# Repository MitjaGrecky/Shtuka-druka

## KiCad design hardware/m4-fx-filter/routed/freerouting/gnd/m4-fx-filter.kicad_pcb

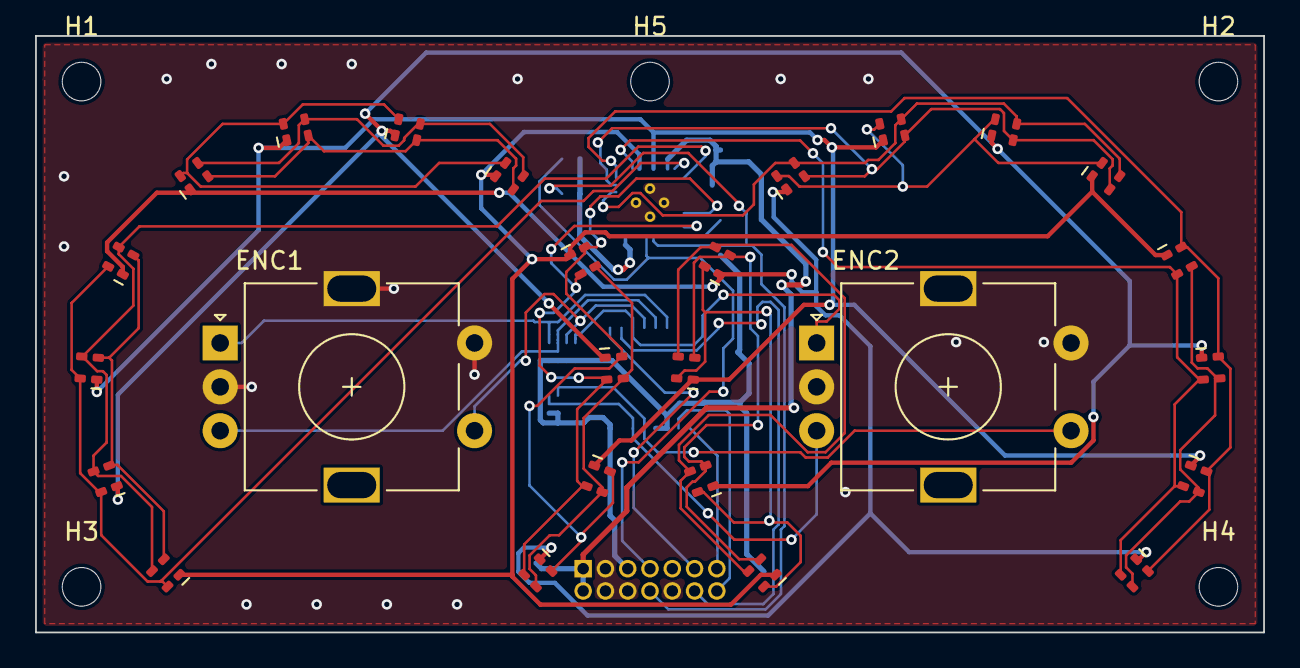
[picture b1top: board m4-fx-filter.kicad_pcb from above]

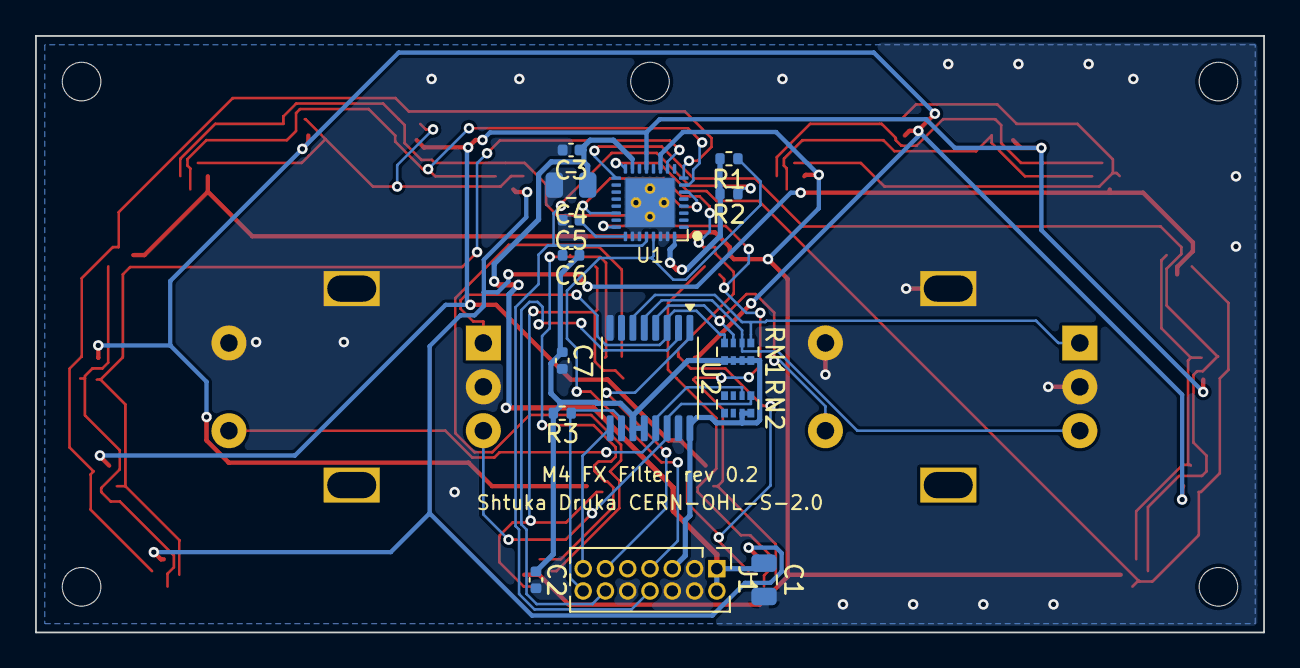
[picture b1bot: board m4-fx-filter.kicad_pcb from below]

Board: 2 copper layers, 70.0 x 34.0 mm, 46 parts (15 on the bottom side), 38 nets.

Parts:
C1: 10u; C_0805_2012Metric
C2, C3, C5: 1u; C_0402_1005Metric
C4: 4.7u; C_0805_2012Metric
C6: 1n; C_0402_1005Metric
C7: 100n; C_0402_1005Metric
D1, D2, D3, D4, D5, D6, D7, D8, D9, D10, D11, D12, D13, D14, D15, D16, D17, D18, D19, D20, D21, D22, D23, D24: XL-1615RGBC-RF; LED_RGB_XL-1615RGBC_1.6x1.5mm
ENC1, ENC2: EC11E smooth, switch; RotaryEncoder_Alps_EC11E-Switch_Vertical_H20mm_Ring
H1, H2, H3, H4, H5: M2; MountingHole_2.2mm_M2
J1: Module bus 2x7 1.27; PinHeader_2x07_P1.27mm_Vertical
R1, R2: 4.7k; R_0402_1005Metric
R3: 10k; R_0402_1005Metric
RN1, RN2: 4x10k; R_Array_Convex_4x0402
U1: LP5864RSMR; VQFN-32-1EP_4x4mm_P0.4mm_EP2.8x2.8mm
U2: 74HC165PW; TSSOP-16_4.4x5mm_P0.65mm

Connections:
+3V3: C2.1, C6.1, C7.1, J1.5, R1.2, R2.2, R3.2, RN1.5, RN1.6, RN1.7, RN1.8, RN2.7, RN2.8, U1.32, U2.11, U2.12, U2.16
+5V: C1.1, C3.1, C4.1, J1.1, J1.2, U1.1, U1.15
/A_CS0: D13.1, D14.1, D15.1, D16.1, U1.2
/A_CS1: D13.3, D14.3, D15.3, D16.3, U1.3
/A_CS2: D13.4, D14.4, D15.4, D16.4, U1.4
/A_CS3: D17.1, D18.1, D19.1, D20.1, U1.5
/A_CS4: D17.3, D18.3, D19.3, D20.3, U1.6
/A_CS5: D17.4, D18.4, D19.4, D20.4, U1.7
/A_CS6: D21.1, D22.1, D23.1, D24.1, U1.8
/A_CS7: D21.3, D22.3, D23.3, D24.3, U1.9
/A_CS8: D21.4, D22.4, D23.4, D24.4, U1.10
/A_CS9: D1.1, D2.1, D3.1, D4.1, U1.16
/A_CS10: D1.3, D2.3, D3.3, D4.3, U1.17
/A_CS11: D1.4, D2.4, D3.4, D4.4, U1.18
/A_CS12: D5.1, D6.1, D7.1, D8.1, U1.19
/A_CS13: D5.3, D6.3, D7.3, D8.3, U1.20
/A_CS14: D5.4, D6.4, D7.4, D8.4, U1.21
/A_CS15: D9.1, D10.1, D11.1, D12.1, U1.22
/A_CS16: D9.3, D10.3, D11.3, D12.3, U1.23
/A_CS17: D9.4, D10.4, D11.4, D12.4, U1.24
/A_SW0: D1.2, D8.2, D9.2, D13.2, D20.2, D21.2, U1.11
/A_SW1: D2.2, D7.2, D10.2, D14.2, D19.2, D22.2, U1.12
/A_SW2: D3.2, D6.2, D11.2, D15.2, D18.2, D23.2, U1.13
/A_SW3: D4.2, D5.2, D12.2, D16.2, D17.2, D24.2, U1.14
/A_VCAP: C5.1, U1.25
/E0_A: ENC1.A, RN1.1, U2.6
/E0_B: ENC1.B, RN1.2, U2.5
/E0_SW: ENC1.S1, RN1.3, U2.4
/E1_A: ENC2.A, RN1.4, U2.3
/E1_B: ENC2.B, RN2.1, U2.14
/E1_SW: ENC2.S1, RN2.2, U2.13
/SCL: J1.8, R2.1, U1.28
/SDA: J1.7, R1.1, U1.29
/SR_CLK: J1.12, U2.2
/SR_IN: J1.14, R3.1, U2.10
/SR_OUT: J1.13, U2.9
/~SR_LOAD: J1.11, U2.1
GND: C1.2, C2.2, C3.2, C4.2, C5.2, C6.2, C7.2, ENC1.C, ENC1.MP, ENC1.S2, ENC2.C, ENC2.MP, ENC2.S2, J1.3, J1.4, J1.6, J1.10, U1.26, U1.27, U1.30, U1.31, U1.33, U2.8, U2.15

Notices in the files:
hardware/m4-fx-filter/routed/freerouting/gnd/m4-fx-filter.kicad_pcb:
Shtuka Druka - open hardware, CERN-OHL-S-2.0
Shtuka Druka CERN-OHL-S-2.0
